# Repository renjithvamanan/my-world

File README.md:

# my-world
My experiments, creativity, DIYs, software/firmware/hardware developments everything comes under this repository.

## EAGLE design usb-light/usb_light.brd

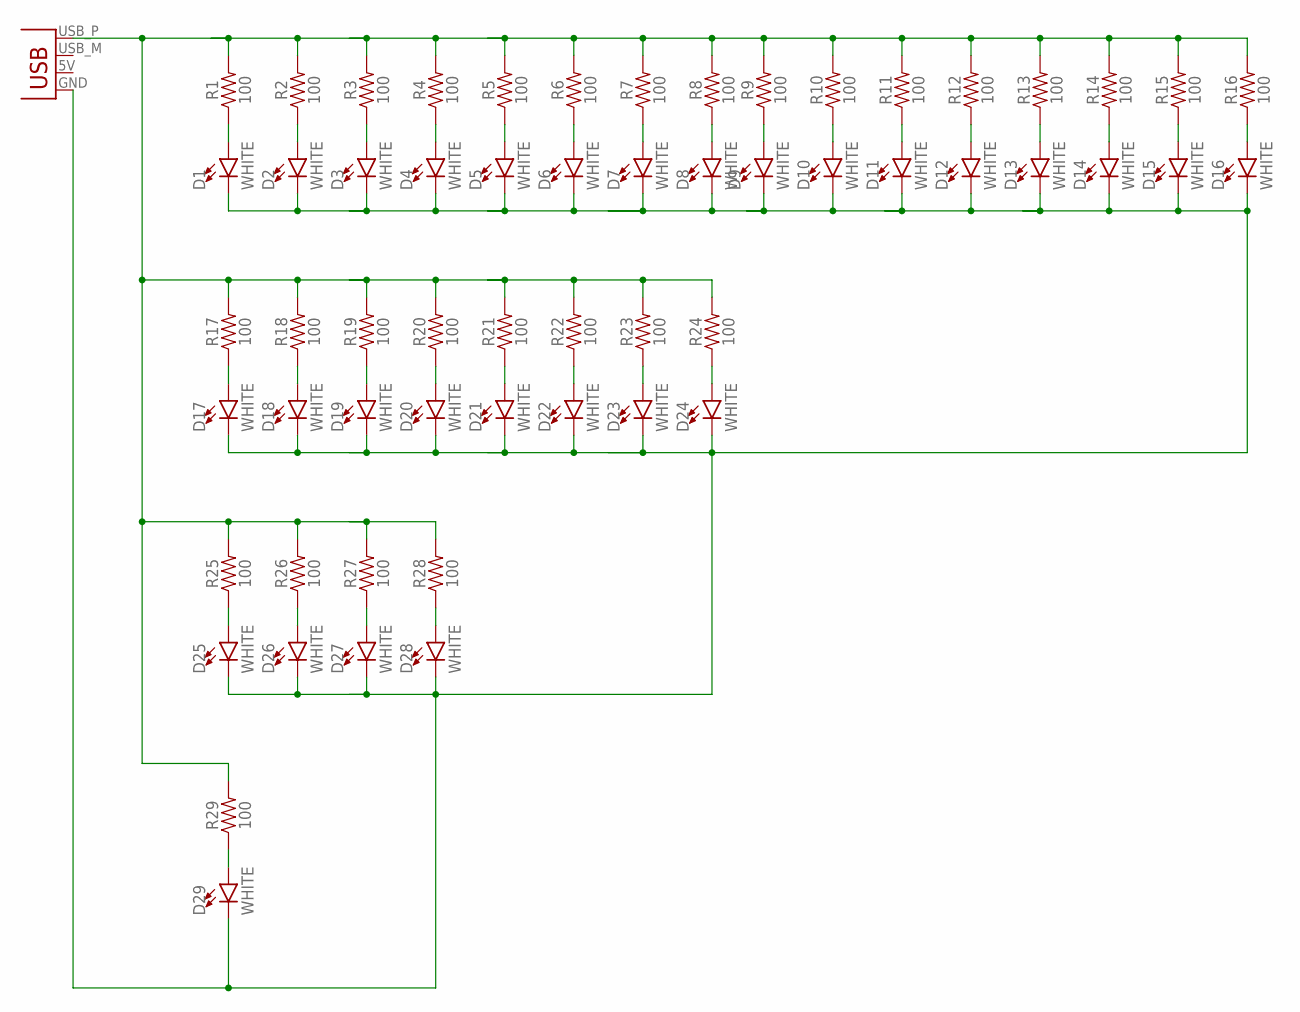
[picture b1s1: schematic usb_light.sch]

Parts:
D1, D2, D3, D4, D5, D6, D7, D8, D9, D10, D11, D12, D13, D14, D15, D16, D17, D18, D19, D20, D21, D22, D23, D24, D25, D26, D27, D28, D29: WHITE; LED-1206
R1, R2, R3, R4, R5, R6, R7, R8, R9, R10, R11, R12, R13, R14, R15, R16, R17, R18, R19, R20, R21, R22, R23, R24, R25, R26, R27, R28, R29: 100; 1206
USB: USBPCB; USB-A-PCB

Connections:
unnamed: D1.A, R1.1
unnamed: D1.C, D2.C, D3.C, D4.C, D5.C, D6.C, D7.C, D8.C, D9.C, D10.C, D11.C, D12.C, D13.C, D14.C, D15.C, D16.C, D17.C, D18.C, D19.C, D20.C, D21.C, D22.C, D23.C, D24.C, D25.C, D26.C, D27.C, D28.C, D29.C, USB.GND
unnamed: R1.2, R2.2, R3.2, R4.2, R5.2, R6.2, R7.2, R8.2, R9.2, R10.2, R11.2, R12.2, R13.2, R14.2, R15.2, R16.2, R17.2, R18.2, R19.2, R20.2, R21.2, R22.2, R23.2, R24.2, R25.2, R26.2, R27.2, R28.2, R29.2, USB.USB_P (D+)
unnamed: D2.A, R2.1
unnamed: D17.A, R17.1
unnamed: D3.A, R3.1
unnamed: D18.A, R18.1
unnamed: D4.A, R4.1
unnamed: D19.A, R19.1
unnamed: D20.A, R20.1
unnamed: D5.A, R5.1
unnamed: D21.A, R21.1
unnamed: D22.A, R22.1
unnamed: D6.A, R6.1
unnamed: D23.A, R23.1
unnamed: D24.A, R24.1
unnamed: D7.A, R7.1
unnamed: D25.A, R25.1
unnamed: D8.A, R8.1
unnamed: D26.A, R26.1
unnamed: D9.A, R9.1
unnamed: D27.A, R27.1
unnamed: D28.A, R28.1
unnamed: D10.A, R10.1
unnamed: D29.A, R29.1
unnamed: D11.A, R11.1
unnamed: D12.A, R12.1
unnamed: D13.A, R13.1
unnamed: D14.A, R14.1
unnamed: D15.A, R15.1
unnamed: D16.A, R16.1

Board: 2 copper layers, 59 parts (0 on the bottom side), 31 nets, no tracks yet.

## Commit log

2018-09-01 This is my first commit.
2018-09-04 Just started working on it
2018-09-05 Modifications done
2018-09-06 Almost added the frame part.
2018-09-07 Adding the container part.
2018-09-09 Almost finished with frame and S size tray.
2018-09-10 Started working on the L Size Box.
2018-09-10 Resync with the unwanted branch created...
2018-09-10 Trying to commit to master somehow...Git is complicated ?
2018-09-10 Almost finished with tray sizes S and L
2018-09-10 Finishing touches on going.
2018-09-11 Fill colour removed. Added Stroke style and colour Added text details.
2018-09-11 Recovered version
2018-09-12 Added USB Light files
2018-09-16 Applying learning from the test cuts from Fablab.
2018-09-17 Resizing the bpx for max utilization
2018-09-18 Size alterations further
2018-09-19 Size alterations ongoing
2018-09-20 Finalizing size alterations
2018-09-21 Finalizing the sizes
2018-09-21 Corrected laser kerf
2018-09-23 I was almost ready to go to Fablab with my files. But still have got some confusion on the kerf related design.
2018-09-28 Added test files
2018-10-23 Redesigned the box to a simple version
2021-04-09 First file commit

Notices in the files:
parts and their libraries:
SparkFun-LED: Licensing: Creative Commons ShareAlike 4.0 International - https://creativecommons.org/licenses/by-sa/4.0
